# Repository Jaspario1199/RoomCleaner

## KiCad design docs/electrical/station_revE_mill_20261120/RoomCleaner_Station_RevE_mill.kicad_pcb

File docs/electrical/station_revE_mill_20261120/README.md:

# RoomCleaner Station Rev E, mill variant: double-sided board milled in-house on the Fab Lab Carvera

**Same circuit, same parts and same placement as Rev E (`../station_revE_pcb_20261029/`), re-laid out
so that it can be milled from double-sided FR4 (copper / insulator / copper) on the lab's Makera Carvera.
There is no through-hole plating, so every via becomes a soldered wire and every through-hole pin connects
only on the side it is soldered on.** SMD parts still go through the lab's stencil → NeoDen YY1 → DDM
Novastar flow; the rest is hand-soldered at the bench.

## Why this variant exists

Rev E is laid out for a board house: plated vias, copper on both sides of every through-hole pin, 51
stitching vias, solder mask. A milled board has none of that. Without plating:

* a via is only a hole: it connects top and bottom only after a wire (or a via rivet) is soldered on both
  sides;
* a pin of a female header, JST-XH connector, screw terminal or C1 connects only where it is soldered.
  Their bodies sit flush on the top, so they can only be soldered on the bottom.

This variant makes every through-hole pad single-sided (bottom copper only), keeps the SMD parts on top,
and joins the two with as few wire vias as the routing allows. Use it if the lab approves FR4 on the
Carvera and a board is wanted faster than a board-house order. The Rev E board-house files stay the
reference for a production run.

Renders: top = F.Cu + paste, bottom = B.Cu seen from below; both with the outline, the 90 x 70 mm stock and
the two registration pins (grey). On the top render the round white areas are the copper-free keep-outs
over the bottom-only pins (the pins pass through bare FR4 on the top side). No silkscreen or mask: the
milled board has none.

## Files

| File | What |
|---|---|
| `RoomCleaner_Station_RevE_mill.zip` | **for the lab's CAM step**: `_F_Cu.gbr`, `_B_Cu.gbr`, `_Edge_Cuts.gbr`, `_F_Paste.gbr` (stencil, SMD pads only), `_ALL-NPTH.drl` (one Excellon file, every hole, all non-plated, including the two 3.0 mm registration-pin holes), `_Registration_User_Drawings.gbr` (stock rectangle, flip axis, pins; reference only). All files share one origin: **the lower-left board corner, X right, Y up, mm**. |
| `RoomCleaner_Station_RevE_mill_pos.csv` | YY1 placement, top, SMD only, mm, same origin (`kicad-cli pcb export pos --side front --smd-only --use-drill-file-origin`). R1-R4, D1, plus FID1-FID3 rows (fiducials, not parts). |
| `RoomCleaner_Station_RevE_mill_F.Cu_mirrored_1to1.pdf`, `_B.Cu_mirrored_1to1.pdf` | fallback 1:1 copper artwork (A4, black on white, with outline, stock and pin marks), each in the orientation for a face-down transfer (toner transfer / photo-resist film): F.Cu mirrored; B.Cu in top view, which is the mirror image of the bottom as seen from below. Print at 100 % ("actual size") and check 70.0 x 50.0 mm on the outline. |
| `RoomCleaner_Station_RevE_mill_top.png`, `_bottom.png` | renders (above) |
| `RoomCleaner_Station_RevE_mill.kicad_pro/.kicad_pcb/.kicad_prl`, `fp-lib-table`, `RoomCleanerRevEMill.pretty/` | KiCad 7 project; generated footprints with single-sided pads |
| `RoomCleaner_Station_RevE_mill_BOM.csv` | BOM (same parts as Rev E) + 11 wire vias |
| `RoomCleaner_Station_RevE_mill_drc.rpt` | KiCad DRC: **0 violations, 0 unconnected** |
| `netlist_check.txt` | geometric net check vs Rev D: **PASS** |
| `mill_check.txt` | top-copper check, mill rules, wire-via list: **PASS** |
| `build_pcb_revE_mill.py` | builds everything from the Rev D nets, re-using the Rev E generator and router by import |
| `check_pcb_revE_mill.py` | runs the Rev E net checker on this board + the mill checks |
| `routing_mill.json` | cached router result |

```
cd docs/electrical/station_revE_mill_20261120
/usr/bin/python3.12 build_pcb_revE_mill.py             # board, DRC, exports (re-uses routing_mill.json)
/usr/bin/python3.12 build_pcb_revE_mill.py --reroute   # route again (about 5 min)
/usr/bin/python3.12 check_pcb_revE_mill.py             # net check + mill checks
```
(`python3.12`: KiCad 7.0.11's `pcbnew` module is built for it on this machine.)

## Results

* **KiCad DRC (7.0.11): 0 violations, 0 unconnected pads.** Rules in the project: clearance 0.4 mm
  (0.5 mm for power, 5 V and GND classes), 0.5 mm to the board edge, keep-outs over single-sided pins.
* **Net check: PASS.** The Rev E checker (imported unchanged) joins copper by geometry; a pad joins
  only the copper layer it is on, a via joins both layers (the soldered wire). 16 copper islands = the 16
  Rev D nets, pin for pin; the 6 open Rev D pins touch nothing; no shorts. Mutation tests: removing one
  HOME wire via gives "HOME split into 2 copper islands", FAIL; a top track onto XIAO pin 5 is caught by
  the top-copper check, FAIL.
* **Top-copper check: PASS.** No F.Cu copper (track, via pad, SMD pad, pour, copper text) comes within
  0.4 mm of any pad of J1, J2, J3, J5, U1, U2, U3 or C1, or of the other bottom-only pads (JP1 pin 2,
  TP1-TP4); none of those pads has top copper. Closest: 0.44 mm (top GND pour to J1 pin 1). Mirrored check
  for the one top-only pad (JP1 pin 1): no bottom copper within 0.4 mm.
* **Wire vias: 11** (0 stitching vias). See "Rules not met".
* Mill rules: tracks 1.2 mm (+12V/VMOT, coils), 0.8 mm (5VB, 5VD, +5V, GND), 0.6 mm (signals, +3V3);
  drills 0.8 / 1.0 / 1.3 mm, 3.2 mm M3 holes, 3.0 mm registration holes; THT pads 2.0 mm (terminal
  2.6 mm, test pads 2.5 mm), annular ring ≥ 0.5 mm; wire vias 2.0 mm pads / 0.8 mm drill, every via pad
  ≥ 2.0 mm from every part body (courtyard). GND pour on both layers: 0.5 mm clearance, 0.6 mm minimum
  width, 0.8 mm thermal spokes, islands removed. 789 mm of track.

## Wire vias (W1-W11)

Coordinates in mm. "Top" = from the top-left board corner, y down (KiCad view). "File" = Gerber/drill
origin (lower-left corner, Y up). On the flipped stock (side 2) the same hole is at X' = 70 − X.

| Via | Net | x, y (top) | X, Y (file) | Nearest part body |
|---|---|---|---|---|
| W1 | +3V3 | 15.24, 38.35 | 15.24, 11.65 | J5, 3.5 mm |
| W2 | +3V3 | 29.72, 36.07 | 29.72, 13.93 | R4, 2.2 mm |
| W3 | +3V3 | 56.90, 42.16 | 56.90, 7.84 | TP4, 3.2 mm |
| W4 | 5VB | 25.65, 16.51 | 25.65, 33.49 | TP2, 2.2 mm |
| W5 | DIR | 35.81, 33.53 | 35.81, 16.47 | U3 socket, 2.1 mm |
| W6 | EN | 11.68, 30.23 | 11.68, 19.77 | U2 socket, 2.2 mm |
| W7 | EN | 34.54, 15.75 | 34.54, 34.25 | U3 socket, 2.05 mm |
| W8 | GND | 34.54, 19.56 | 34.54, 30.44 | U3 socket, 2.05 mm |
| W9 | HOME | 21.08, 39.88 | 21.08, 10.12 | J5, 2.0 mm |
| W10 | HOME | 31.75, 19.56 | 31.75, 30.44 | U3 socket, 4.8 mm |
| W11 | STEP | 34.54, 22.35 | 34.54, 27.65 | U3 socket, 2.05 mm |

The distances are pad edge to courtyard; the plug-in modules count as part bodies over their whole
outline, so no via sits under the XIAO or the A4988 (`mill_check.txt` is the generated version of this table).

## Rules not met, and design changes forced by the mill rules

**Via count: 11, target was ≤ 6. The target cannot be met with this circuit and these rules.** Every
SMD pad is on top and every through-hole pad is on the bottom, so each net that touches an SMD part needs
at least one wire via. Those nets are +3V3 (R1, R4), EN (R1), STEP (R2), DIR (R3), HOME (R4), GND (R2,
R3), 5VB and 5VD (D1): 8 nets. The JP1 exception below takes 5VD off that list, so **the floor is 7**.
The other 4 come from crossings the bottom layer cannot make. The router lets each crossing go over the top
through an SMD net's top-side copper, which costs 1 via. A plain jumper would cost 2:

* EN (W6 + W7): the XIAO's EN pin lies on the far side of its STEP/DIR pins from the A4988's EN pin, at
  the top of the A4988 logic column;
* HOME (W9 + W10): XIAO D10 is on the module's top pin row and has to cross the XIAO → A4988 signal bundle
  to reach J3 at the bottom edge;
* +3V3 (W1-W3): 3V3 goes to J5 at the bottom left, to R1/R4 and to the A4988 VDD pin on the motor side.
  The VDD pin sits between the coil and GND pins, and the 1A/1B coil pair has to cross (A4988 order
  2B 2A 1A 1B vs. J2 order 2B 2A 1B 1A).

Several router settings were tried: via price 220/500 grid cells, other net orders, vias under the
modules allowed or not, test-pad moves, and a greedy rip-up pass after routing. The result never went
below 11. Fewer vias would need a different placement (for example the A4988 turned 90°, or J3 and J5
swapped together with a new connector pinout) or connector pins soldered on top. Both change Rev E
decisions, so they are left to the lead.

Changes vs Rev E (placement, values and nets unchanged):

1. **Every THT pad single-sided.** Sockets, JST-XH, terminal, C1, test pads, JP1 pin 2: B.Cu only.
   Each one has an F.Cu keep-out of pad radius + 0.45 mm (no track, via or pour). The whole board was
   re-routed for this. Rev E routed freely on both layers.
2. **JP1 pin 1 is the one documented exception: top copper only.** It is the D1-cathode side (5VD), and
   D1 is on top, so 5VD needs no via. A 2-pin male header can be soldered on top: slide its plastic
   spacer up the pins about 2 mm before soldering. The pad is round now (Rev E: square pin-1 pad), with a
   0.45 mm bottom keep-out. Pin 2 (+5V) is soldered on the bottom as usual.
3. **Vias: 7 plated 1.0/0.5 mm routing vias + 51 stitching vias → 11 wire vias 2.0/0.8 mm, no
   stitching.** The top GND pour connects through W8 and the R2/R3 GND pads only.
4. **Test pads TP1-TP4 are bottom-only**: probe them from below.
5. GND pour: thermal spokes 0.6 → 0.8 mm, minimum pour width 0.5 → 0.6 mm (easier to mill).
6. **Copper labels added** (top: +12V, GND, VMOT, C1+, O+, JP1 ON=12V, USB, ENC, SW, MOTOR, 1A, board
   name and date; bottom: "BOTTOM E-MILL", which reads correctly from below). Strokes 0.35-0.4 mm, 1.2-1.6 mm
   high: a 0.2 mm V-bit can cut them. They are cosmetic, so if the CAM drops a letter, nothing
   breaks. The silkscreen of Rev E stays in the KiCad file as documentation only.
7. Outputs: no mask or silkscreen Gerbers; one non-plated drill file instead of PTH + NPTH; registration
   holes added (drill file only, outside the board outline).
8. Fiducials FID1-FID3 kept: bare 1 mm copper dots with a 1.5 mm copper-free ring, for the stencil and
   the YY1.

## Carvera workflow (lab CAM step)

**Before anything: lab staff must confirm** (1) that FR4 is approved on the Carvera (the lab docs list
FR4 / composites as pending; glass-fibre dust needs the dust shoe / vacuum, no compressed air, and a mask
when cleaning up), (2) which bits they stock and allow for PCB work, and (3) the smallest trace and gap
they can hold. **This design needs: trace ≥ 0.6 mm, gap ≥ 0.4 mm (0.5 mm around power), drills 0.8 / 1.0 /
1.3 mm, 3.0 and 3.2 mm holes, and a 70 x 50 mm outline cut.**

1. Hand the zip to the staff member doing CAM. The lab's CAM is Fusion 360 (Manufacture). There is no
   Gerber-to-toolpath tool in this repository (no FlatCAM-style output), so turning the Gerbers into
   toolpaths is **the lab's own CAM step**. It needs: isolation of `F_Cu`, isolation of `B_Cu`
   (mirrored, see below), drilling from `ALL-NPTH.drl` sorted by tool, and the profile from `Edge_Cuts`.
   If their Fusion path takes DXF better than Gerber, KiCad exports DXF from the same project:
   `kicad-cli pcb export dxf -l F.Cu,Edge.Cuts --ou mm -o F_Cu.dxf RoomCleaner_Station_RevE_mill.kicad_pcb`
   (same for `B.Cu`). KiCad 7's DXF keeps KiCad's page coordinates, so re-zero it on the lower-left corner
   of the outline (it is in the same DXF). Every job must use that corner as its origin.
2. Suggested tools (staff decide): isolation with a 0.2 mm 30° V-bit or a ≤ 0.4 mm end mill (the
   narrowest gap is 0.4 mm); 0.8 / 1.0 / 1.3 mm drills; 3.0 and 3.2 mm holes helically milled with a
   1-2 mm end mill or drilled; profile with a 1.5-3.175 mm end mill, with 2-4 tabs. Clearing the copper
   between isolation passes is not needed: the pours are GND or floating.
3. Use the Carvera's surface probing (Z / height map) on the copper before isolation, if staff use it:
   the isolation depth on FR4 is shallow, and boards are rarely flat.

## Two-sided registration (flip and pins)

Stock 90 x 70 mm, the board centred in it: in file coordinates the stock runs from (−10, −10) to
(80, 60). Two 3.0 mm registration-pin holes lie on the flip axis X = 35 (the board's vertical centre
line), outside the board:

| Pin | X, Y (file) |
|---|---|
| REG1 | 35.0, −5.5 |
| REG2 | 35.0, 54.5 |

1. Fix a sacrificial spoilboard (MDF) to the bed and face it. Fix the stock with double-sided tape
   (or clamps outside the stock). Set the work XY zero at the lower-left board corner, 10 mm in from the
   stock's lower-left corner. **Do not change the spoilboard or the XY zero until both sides are done.**
2. **Side 1 = top (F.Cu) up:** drill every hole from `ALL-NPTH.drl`. Drill REG1 and REG2 through the
   stock and about 3 mm into the spoilboard. Then isolate F.Cu.
3. Lift the stock off and **flip it left-right** (turn it over about the vertical line X = 35). Push two
   3.0 mm dowel pins (or 3.0 mm drill shanks) through REG1/REG2 into the spoilboard holes and tape the
   stock down again. The pins are not symmetric top-to-bottom (5.5 mm below the board, 4.5 mm above), so
   a wrong flip (top-to-bottom) leaves both holes 1 mm off and the stock will not go onto the pins.
4. **Side 2 = bottom (B.Cu) up:** use the B.Cu job mirrored about X = 35 in the same zero (X' = 70 − X,
   Y unchanged); the pins map onto themselves. Before cutting, jog to one via (e.g. W8 at X' = 35.46,
   Y = 30.44) and check that the tool sits centred on the drilled hole. Then isolate B.Cu.
5. Cut the profile last, from side 2 (the outline is symmetric, mirrored or not), and break the tabs.
   Pads are 2.0 mm on 0.8-1.3 mm holes: registration within about ±0.3 mm still leaves a usable ring.

## Assembly order

1. **Mill and drill** (above).
2. **Clean**: deburr both sides (fine abrasive pad), wash with IPA, let dry. Look for copper slivers under
   a magnifier. Fluke on continuity (bottom side): TP1 (12V), TP2 (5V) and TP3 (3V3) to TP4 (GND) must
   be open. Also check the motor coil tracks against each other.
3. **Wire vias W1-W11**: a short piece of 0.6-0.7 mm bare tinned copper wire (a resistor lead works)
   or a 0.8 mm via rivet in each 0.8 mm hole. Solder top and bottom, then trim flush. **On top, keep each
   joint low (file it flat, ≤ 0.3 mm)**: W2, W4, W5, W7, W8 and W11 sit 2.05-2.2 mm from R2/R3/R4/TP2 and
   the stencil has to lie flat around them. Check each via end to end with the meter (0 Ω top pad to
   bottom pad). If the stencil does not lie flat, solder the vias after reflow instead (they are ≥ 2 mm
   from every part).
4. **Stencil + SMD + reflow** (top): stencil from `F_Paste.gbr` (10 pads: R1-R4 1206, D1 SMA). It can be
   cut in the lab if staff have a film-stencil process, or ordered. Bare copper oxidises: wipe the pads
   with IPA just before printing, SAC305 paste. YY1: `RoomCleaner_Station_RevE_mill_pos.csv`, the same
   origin as the Gerbers, fiducials FID1-FID3; two feeders (10k 1206, SS14 SMA). **D1: the cathode band
   goes to pad 1, toward JP1.** Reflow with the lab's SAC305 profile on the Novastar. The via joints melt
   again, so check them after reflow.
5. **JP1** (the top-soldered exception): slide the black spacer about 2 mm up the pins, insert from the
   top, solder **pin 1 on the top** (the pad with the track from D1) and **pin 2 on the bottom**. Leave the
   spacer where it stops.
6. **THT on the bottom only**, lowest first: C1 (100 µF; "+" is the square pad, copper label "C1+"),
   female headers U1 1x5, U2 2 x 1x7, U3 2 x 1x8, JST-XH J5, J3, J2, terminal J1. Every pin is soldered
   **only on the bottom**: the top side of these pins is bare FR4 on purpose. Seat each header pair with
   its module plugged in. **Do not solder any module.**

## First power-up (Kungber SPS3010, Fluke 17B+)

Same as Rev E, with the test pads probed from below:

1. **No modules, JP1 jumper OFF, no motor.** Ohms: TP1 (12V) to TP4 (GND) is not a short; TP2 (5V) and
   TP3 (3V3) to TP4 are not shorts.
2. Supply **12.0 V, 0.3 A current limit**, output off. J1: red to "+12V", black to "GND". Output on:
   about 0 mA; TP1 to TP4 reads 12.0 V.
3. Output off, **plug in the DROK buck** (O+ at the "O+" label). Output on: TP2 reads 5.00 V. Trim to 5.00 V
   before anything else is plugged in. Output off.
4. **Plug in the XIAO** (USB-C at the left edge, "USB" label). For 12 V operation **JP1 ON**; with a USB
   cable in the XIAO, **JP1 OFF**. Output on: TP3 reads 3.3 V; the current stays well under 0.3 A.
5. Output off. **Motor to J2 first, then the A4988**, with its VMOT pin at the "VMOT" label (top right of
   the socket). Output on, still at 0.3 A. The firmware holds EN high until armed, so the current stays
   low. Set Vref per DECISIONS D37 (1.5 A). **Raise the limit to 2 A only once the idle current looks
   normal.**
6. **Never unplug the motor or the A4988 with power on.** If anything reads wrong, check the wire vias
   first (W1-W11, table above). A via soldered on one side only behaves like an open circuit.

## How it was made

`build_pcb_revE_mill.py` imports the Rev E generator (`build_pcb_revE.py`) and its router
(`pathfinder.py`, `maze_router.py`) read-only, and redirects their output folder to this one. The circuit
comes from Rev D's `perfboard_data.py` as in Rev E. On top of Rev E it adds: footprints with B.Cu-only
pads (JP1 pin 1 F.Cu-only); router pins restricted to their pad's layer; obstacles on the other layer
over every single-sided pin; a via price of 500 grid cells; via sites limited to ≥ 2 mm pad-edge distance
from every courtyard and clear of the M3 screw heads; F.Cu/B.Cu keep-out rule areas; copper text; and its
own Excellon writer. The writer is cross-checked against KiCad's drill export for every board hole, then
the registration pins are added. The renders are flat plots (kicad-cli PDF → pdftoppm), not 3D views.
No external routing or CAM tools were used.

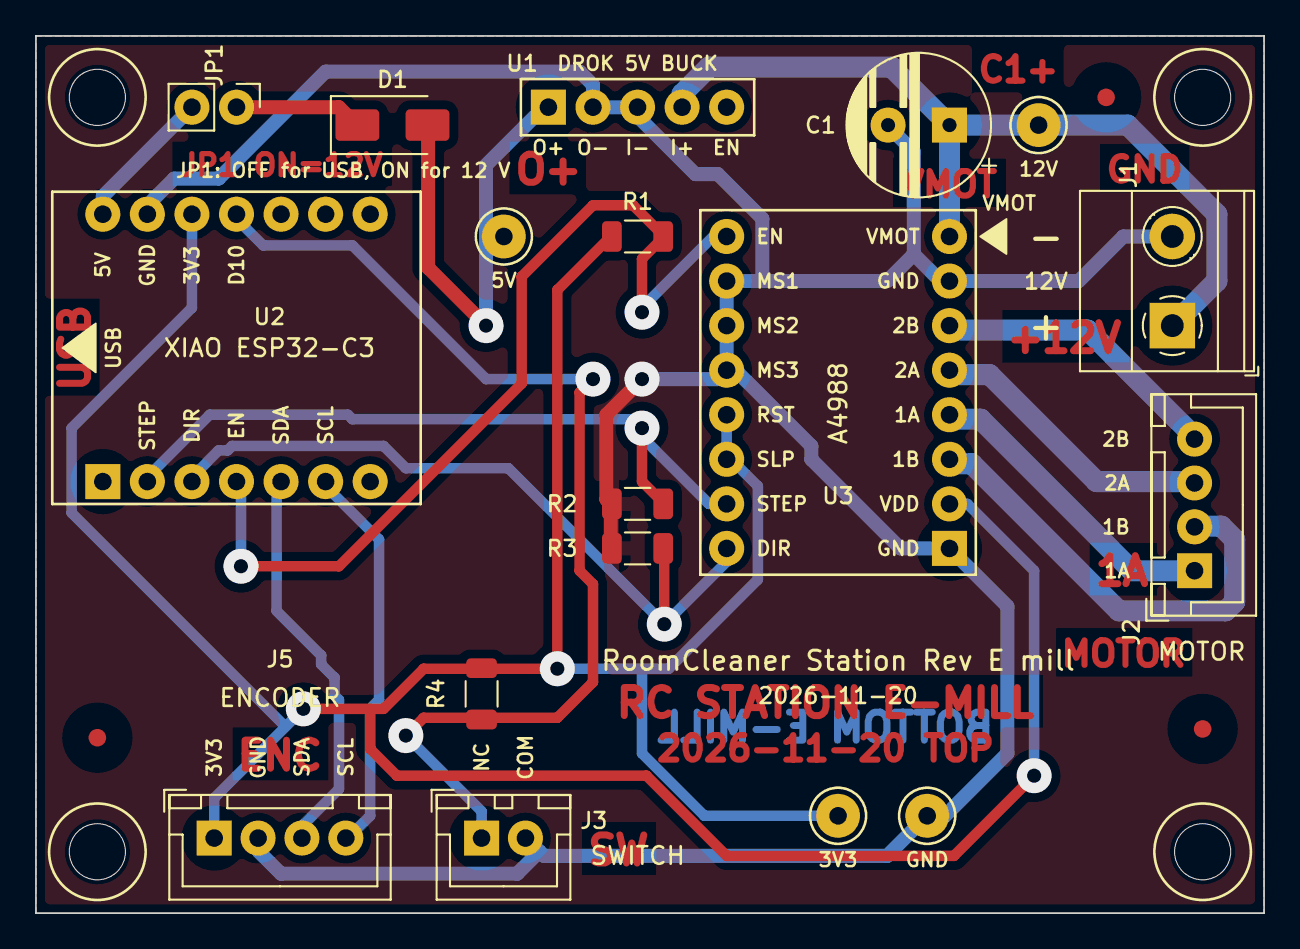
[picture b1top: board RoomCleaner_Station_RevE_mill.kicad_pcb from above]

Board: 2 copper layers, 70.0 x 50.0 mm, 25 parts (0 on the bottom side), 16 nets.

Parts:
C1: 100uF 50V; CP_Radial_D8.0mm_P3.50mm_BigPad
D1: SS14; D_SMA
FID1, FID2, FID3: fiducial; Fiducial_1mm_Mask2mm
H1, H2, H3, H4: M3; MountingHole_3.2mm_M3_NPTH
J1: 12V IN; TerminalBlock_Phoenix_MKDS-1,5-2-5.08_1x02_P5.08mm_Horizont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
J2: MOTOR; JST_XH_B4B-XH-A_1x04_P2.50mm_Vertical_BigPad
J3: SWITCH; JST_XH_B2B-XH-A_1x02_P2.50mm_Vertical_BigPad
J5: ENCODER; JST_XH_B4B-XH-A_1x04_P2.50mm_Vertical_BigPad
JP1: USB/EXT 5V link; PinHeader_1x02_P2.54mm_Vertical_BigPad
R1, R2, R3, R4: 10k; R_1206_3216Metric
TP1: TP 12V; TestPad_THT_D2.5mm_Drill1.0mm
TP2: TP 5V; TestPad_THT_D2.5mm_Drill1.0mm
TP3: TP 3V3; TestPad_THT_D2.5mm_Drill1.0mm
TP4: TP GND; TestPad_THT_D2.5mm_Drill1.0mm
U1: DROK buck 5.00V; DROK_Buck_Socket_1x5
U2: XIAO ESP32-C3; XIAO_ESP32C3_Socket_2x7
U3: A4988 carrier; Pololu_A4988_Socket_2x8

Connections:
5VB: D1.2, TP2.1, U1.1
5VD: D1.1, JP1.1
+3V3: J5.1, R1.1, R4.1, TP3.1, U2.12, U3.2, U3.13, U3.14
+5V: JP1.2, U2.14
+12V: C1.1, J1.1, TP1.1, U1.4, U3.8
DIR: R3.1, U2.3, U3.16
EN: R1.2, U2.4, U3.9
GND: C1.2, J1.2, J3.2, J5.2, R2.2, R3.2, TP4.1, U1.2, U1.3, U2.13, U3.1, U3.7, U3.10, U3.11, U3.12
HOME: J3.1, R4.2, U2.11
M1A: J2.1, U3.4
M1B: J2.2, U3.3
M2A: J2.3, U3.5
M2B: J2.4, U3.6
SCL: J5.4, U2.6
SDA: J5.3, U2.5
STEP: R2.1, U2.2, U3.15

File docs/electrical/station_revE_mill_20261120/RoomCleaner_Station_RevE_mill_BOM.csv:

Process,Reference,Qty/board,Qty/10 boards,Value,Description,Footprint,Manufacturer part,Supplier / note
"machine placed (SMD, top, reflow)",D1,1,10,SS14,"Schottky 40 V 1 A, SMA (replaces 1N5819 DO-41, same function)",Diode_SMD:D_SMA,onsemi SS14 / MDD SS14,LCSC C2480 (verify before ordering)
"machine placed (SMD, top, reflow)",R1 R2 R3 R4,4,40,10k,"10k 1% 1/4 W thick film, 1206",Resistor_SMD:R_1206_3216Metric,Yageo RC1206FR-0710KL,LCSC C17902 (verify before ordering)
"hand soldered (THT, after reflow)",C1,1,10,100uF 50V,"100 uF 50 V aluminium electrolytic, radial 8 mm, 3.5 mm pitch",RoomCleanerRevEMill:CP_Radial_D8.0mm_P3.50mm_BigPad,Panasonic EEU-FR1H101,
"hand soldered (THT, after reflow)",J1,1,10,12V IN,Screw terminal 2-pole 5.08 mm,"RoomCleanerRevEMill:TerminalBlock_Phoenix_MKDS-1,5-2-5.08_1x02_P5.08mm_Horizontal_BigPad","Phoenix Contact 1729128 (MKDS 1,5/ 2-5,08)",
"hand soldered (THT, after reflow)",J2,1,10,MOTOR,"JST-XH 4-pin, top entry",RoomCleanerRevEMill:JST_XH_B4B-XH-A_1x04_P2.50mm_Vertical_BigPad,JST B4B-XH-A(LF)(SN),mating XHP-4 + SXH-001T-P0.6 crimps
"hand soldered (THT, after reflow)",J3,1,10,SWITCH,"JST-XH 2-pin, top entry",RoomCleanerRevEMill:JST_XH_B2B-XH-A_1x02_P2.50mm_Vertical_BigPad,JST B2B-XH-A(LF)(SN),mating XHP-2 + SXH-001T-P0.6 crimps
"hand soldered (THT, after reflow)",J5,1,10,ENCODER,"JST-XH 4-pin, top entry",RoomCleanerRevEMill:JST_XH_B4B-XH-A_1x04_P2.50mm_Vertical_BigPad,JST B4B-XH-A(LF)(SN),mating XHP-4 + SXH-001T-P0.6 crimps
"hand soldered (THT, after reflow)",JP1,1,10,USB/EXT 5V link,1x2 male header 2.54 mm + jumper shunt,RoomCleanerRevEMill:PinHeader_1x02_P2.54mm_Vertical_BigPad,Sullins PRPC002SAAN-RC + QPC02SXGN-RC,
"hand soldered (THT, after reflow)",U1,1,10,DROK buck 5.00V,"Socket: 1x5 female header 2.54 mm (module: DROK mini buck, set to 5.00 V)",RoomCleanerRevEMill:DROK_Buck_Socket_1x5,Sullins PPTC051LFBN-RC,
"hand soldered (THT, after reflow)",U2,2,20,XIAO ESP32-C3,"Socket: 2 x 1x7 female header 2.54 mm (module: Seeed XIAO ESP32-C3, 113991054)",RoomCleanerRevEMill:XIAO_ESP32C3_Socket_2x7,Sullins PPTC071LFBN-RC,2 strips per board
"hand soldered (THT, after reflow)",U3,2,20,A4988 carrier,"Socket: 2 x 1x8 female header 2.54 mm (module: Pololu A4988 carrier, #1182)",RoomCleanerRevEMill:Pololu_A4988_Socket_2x8,Sullins PPTC081LFBN-RC,2 strips per board
not a part,TP1 TP2 TP3 TP4,4,40,test pads,bare pads on bottom copper only (probe from below),,,
not a part,FID1 FID2 FID3,3,30,fiducials,"1 mm bare copper dot, 1.5 mm copper-free ring",,,
not a part,H1 H2 H3 H4,4,40,M3 holes,3.2 mm unplated,,,
modules (plug in),U1 U2 U3,1 each,10 each,"DROK buck, XIAO ESP32-C3, A4988 carrier","plugged into the sockets, not soldered to this board",,,
not a part,W1-W11,11,110,wire vias,"0.6-0.7 mm bare tinned copper wire (or 0.8 mm via rivet) through each 0.8 mm via hole, soldered top and bottom",,,
